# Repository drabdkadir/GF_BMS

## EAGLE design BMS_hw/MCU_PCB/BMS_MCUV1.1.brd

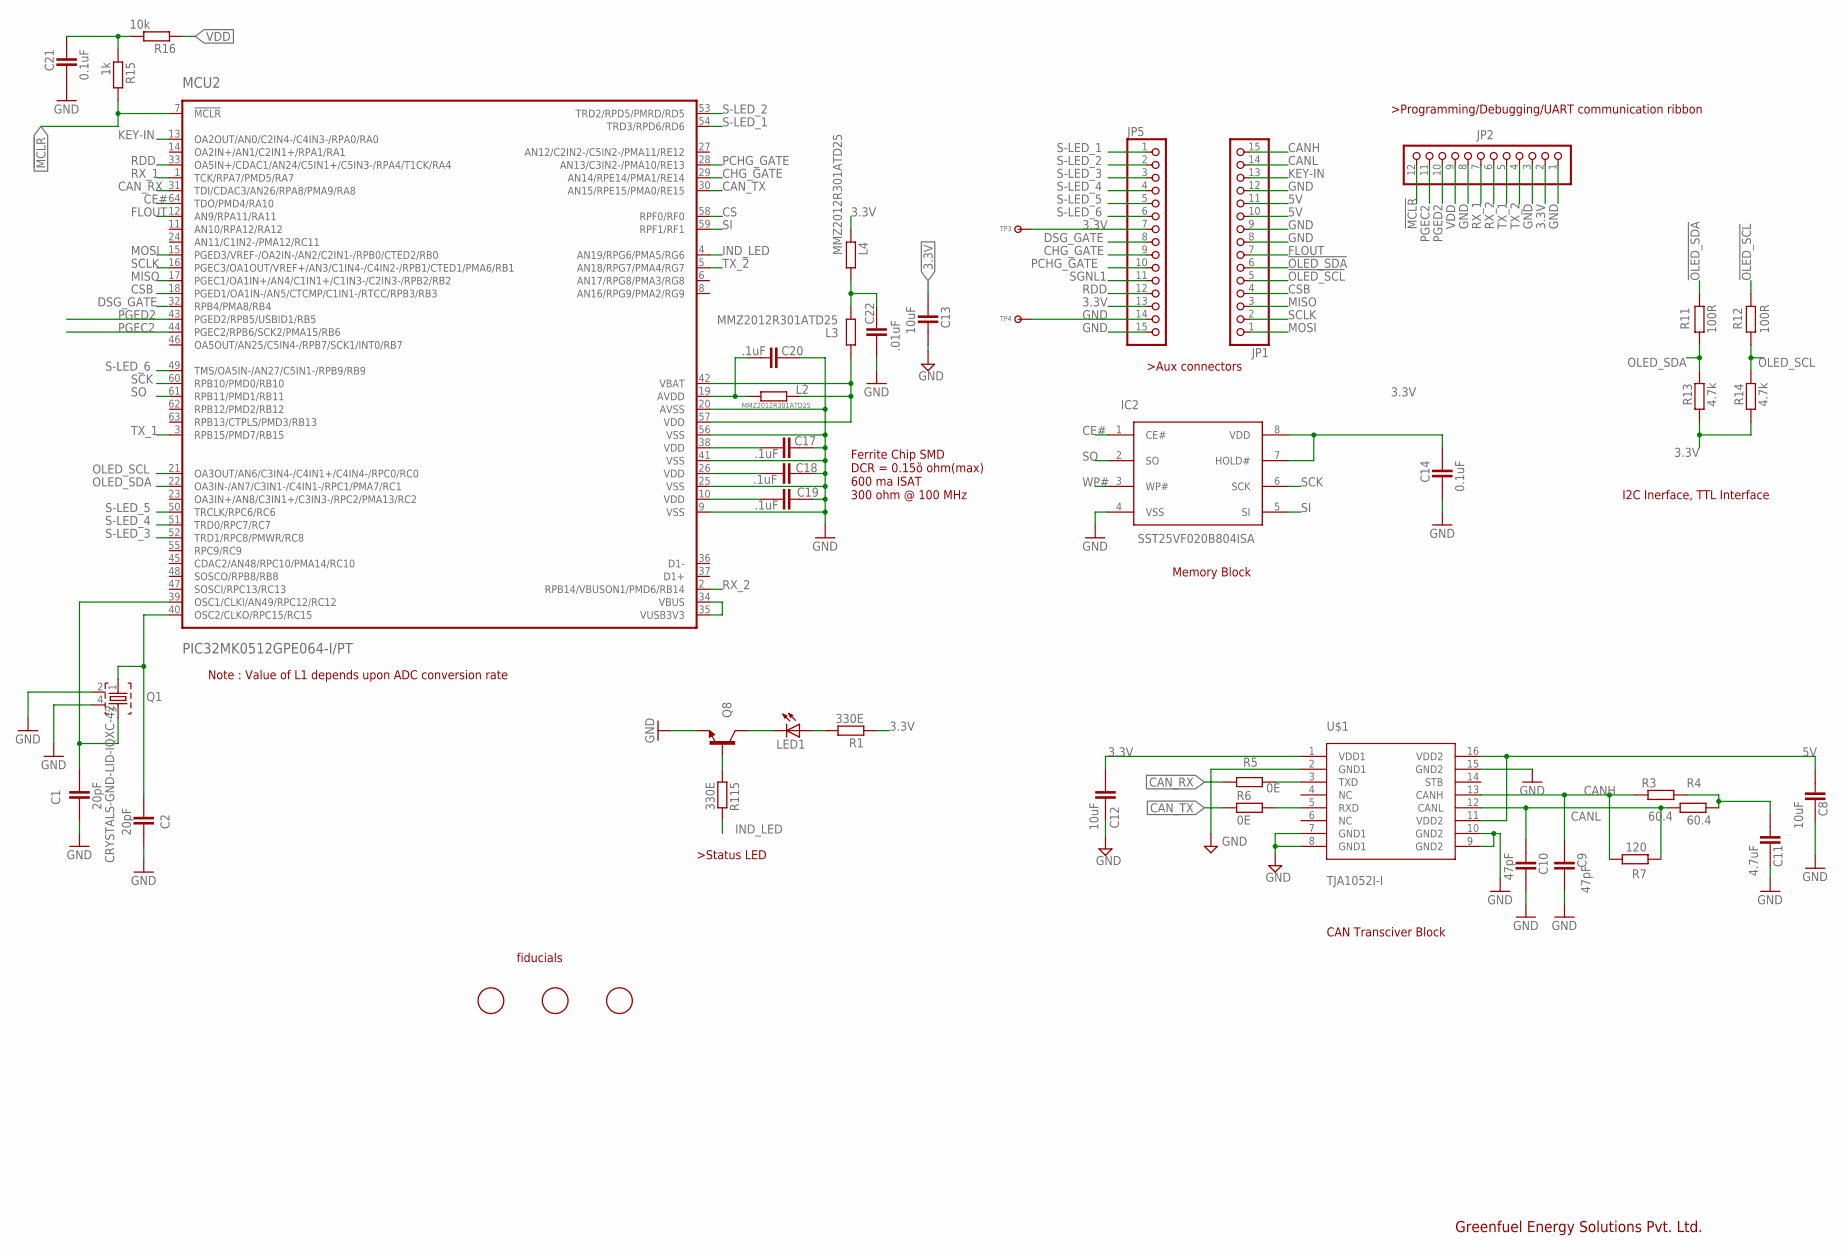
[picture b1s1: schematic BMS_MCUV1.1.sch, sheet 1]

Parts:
C1, C2: 20pF; CAPC1005X60N
C8, C12, C13: 10uF; CAPC1005X60N
C9, C10: 47pF; CAPC1005X60N
C11: 4.7uF; CAPC1005X60N
C14, C21: 0.1uF; CAPC1005X60N
C17, C18, C19, C20: .1uF; CAPC1005X60N
C22: .01uF; CAPC1005X60N
IC2: SST25VF020B804ISA; SOIC127P600X175-8N
JP1, JP5: PINHD-1X15; 1X15
JP2: PINHD-1X12; 1X12X2
L2, L3, L4: MMZ2012R301ATD25; RESC2012X70N
LED1: LEDCHIP-LED0603; CHIP-LED0603
MCU2: PIC32MK0512GPE064-I/PT; TQFP-64-I/PT
Q1: CRYSTALS-GND-LID-IQXC-42; 1.4X1.2-4-PAD
Q8: NPN_SOT-23; SOT95P280X135-3N
R1, R115: 330E; RESC1005X40AN
R3, R4: 60.4; RESC1005X40AN
R5, R6: 0E; RESC1005X40AN
R7: 120; RESC1005X40AN
R11, R12: 100R; RESC1005X40AN
R13, R14: 4.7k; RESC1005X40AN
R15: 1k; RESC1005X40AN
R16: 10k; RESC1005X40AN
TP3, TP4: TP-SMD60
U$1: TJA1052I-I; SOT162-1
U$2, U$3, U$4: FIDUCIAL; FIDUCIAL_1MM

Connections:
3.3V: C12.1, C13.1, C14.1, IC2.7 (HOLD#), IC2.8 (VDD), JP2.2, JP5.7, JP5.13, L4.1, R1.1, R13.1, R14.1, TP3.P$1, U$1.1 (VDD1)
5V: C8.1, JP1.10, JP1.11, U$1.11 (VDD2), U$1.16 (VDD2)
!MCLR: JP2.12, MCU2.7 (!MCLR), R15.2
!OLED_SCL: JP1.5, R12.2
!OLED_SDA: JP1.6, R11.2
AVDD: C20.1, L2.1, MCU2.19 (AVDD)
CANH: C9.1, JP1.15, R3.1, R7.2, U$1.13 (CANH)
CANL: C10.1, JP1.14, R4.1, R7.1, U$1.12 (CANL)
CAN_RX: MCU2.31 (TDI/CDAC3/AN26/RPA8/PMA9/RA8), R5.1
CAN_TX: MCU2.30 (AN15/RPE15/PMA0/RE15), R6.1
CE#: IC2.1 (CE#), MCU2.64 (TDO/PMD4/RA10)
CHG_GATE: JP5.9, MCU2.29 (AN14/RPE14/PMA1/RE14)
CS: MCU2.58 (RPF0/RF0)
CSB: JP1.4, MCU2.18 (PGED1/OA1IN-/AN5/CTCMP/C1IN1-/RTCC/RPB3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)
DSG_GATE: JP5.8, MCU2.32 (RPB4/PMA8/RB4)
FLOUT: JP1.7, MCU2.12 (AN9/RPA11/RA11)
GND: C1.2, C2.2, C8.2, C9.2, C10.2, C11.2, C12.2, C13.2, C14.2, C17.2, C18.2, C19.2, C20.2, C21.2, C22.1, IC2.4 (VSS), JP1.8, JP1.9, JP1.12, JP2.1, JP2.3, JP2.8, JP5.14, JP5.15, MCU2.9 (VSS), MCU2.20 (AVSS), MCU2.25 (VSS), MCU2.41 (VSS), MCU2.56 (VSS), Q1.2, Q1.4, Q8.2 (E), TP4.P$1, U$1.2 (GND1), U$1.7 (GND1), U$1.8 (GND1), U$1.9 (GND2), U$1.10 (GND2), U$1.15 (GND2)
IND_LED: MCU2.4 (AN19/RPG6/PMA5/RG6), R115.2
KEY-IN: JP1.13, MCU2.13 (OA2OUT/AN0/C2IN4-/C4IN3-/RPA0/RA0)
MISO: JP1.3, MCU2.17 (PGEC1/OA1IN+/AN4/C1IN1+/C1IN3-/C2IN3-/R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)
MOSI: JP1.1, MCU2.15 (PGED3/VREF-/OA2IN-/AN2/C2IN1-/RPB0/CTED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)
unnamed: C1.1, MCU2.39 (OSC1/CLKI/AN49/RPC12/RC12), Q1.3
unnamed: C2.1, MCU2.40 (OSC2/CLKO/RPC15/RC15), Q1.1
unnamed: R5.2, U$1.3 (TXD)
unnamed: LED1.A, R1.2
unnamed: R6.2, U$1.5 (RXD)
unnamed: Q8.1 (B), R115.1
unnamed: LED1.C, Q8.3 (C)
unnamed: C22.2, L3.2, L4.2
unnamed: C21.1, R15.1, R16.2
unnamed: MCU2.34 (VBUS), MCU2.35 (VUSB3V3)
OLED_SCL: MCU2.21 (OA3OUT/AN6/C3IN4-/C4IN1+/C4IN4-/RPC0/RC0), R12.1, R14.2
OLED_SDA: MCU2.22 (OA3IN-/AN7/C3IN1-/C4IN1-/RPC1/PMA7/RC1), R11.1, R13.2
PCHG_GATE: JP5.10, MCU2.28 (AN13/C3IN2-/PMA10/RE13)
PGEC2: JP2.11, MCU2.44 (PGEC2/RPB6/SCK2/PMA15/RB6)
PGED2: JP2.10, MCU2.43 (PGED2/RPB5/USBID1/RB5)
R4/R3/C11: C11.1, R3.2, R4.2
RDD: JP5.12, MCU2.33 (OA5IN+/CDAC1/AN24/C5IN1+/C5IN3-/RPA4/T1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)
RX_1: JP2.7, MCU2.1 (TCK/RPA7/PMD5/RA7)
RX_2: JP2.6, MCU2.2 (RPB14/VBUSON1/PMD6/RB14)
S-LED_1: JP5.1, MCU2.54 (TRD3/RPD6/RD6)
S-LED_2: JP5.2, MCU2.53 (TRD2/RPD5/PMRD/RD5)
S-LED_3: JP5.3, MCU2.52 (TRD1/RPC8/PMWR/RC8)
S-LED_4: JP5.4, MCU2.51 (TRD0/RPC7/RC7)
S-LED_5: JP5.5, MCU2.50 (TRCLK/RPC6/RC6)
S-LED_6: JP5.6, MCU2.49 (TMS/OA5IN-/AN27/C5IN1-/RPB9/RB9)
SCK: IC2.6 (SCK), MCU2.60 (RPB10/PMD0/RB10)
SCLK: JP1.2, MCU2.16 (PGEC3/OA1OUT/VREF+/AN3/C1IN4-/C4IN2-/RP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)
SGNL1: JP5.11
SI: IC2.5 (SI), MCU2.59 (RPF1/RF1)
SO: IC2.2 (SO), MCU2.61 (RPB11/PMD1/RB11)
TX_1: JP2.5, MCU2.3 (RPB15/PMD7/RB15)
TX_2: JP2.4, MCU2.5 (AN18/RPG7/PMA4/RG7)
VDD: C17.1, C18.1, C19.1, JP2.9, L2.2, L3.1, MCU2.10 (VDD), MCU2.26 (VDD), MCU2.38 (VDD), MCU2.42 (VBAT), MCU2.57 (VDD), R16.1
WP#: IC2.3 (WP#)

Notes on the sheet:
Note : Value of L1 depends upon ADC conversion rate
CAN Transciver Block
Memory Block
I2C Inerface, TTL Interface
Ferrite Chip SMD DCR = 0.15ȍ ohm(max) 600 ma ISAT 300 ohm @ 100 MHz
Greenfuel Energy Solutions Pvt. Ltd.
fiducials

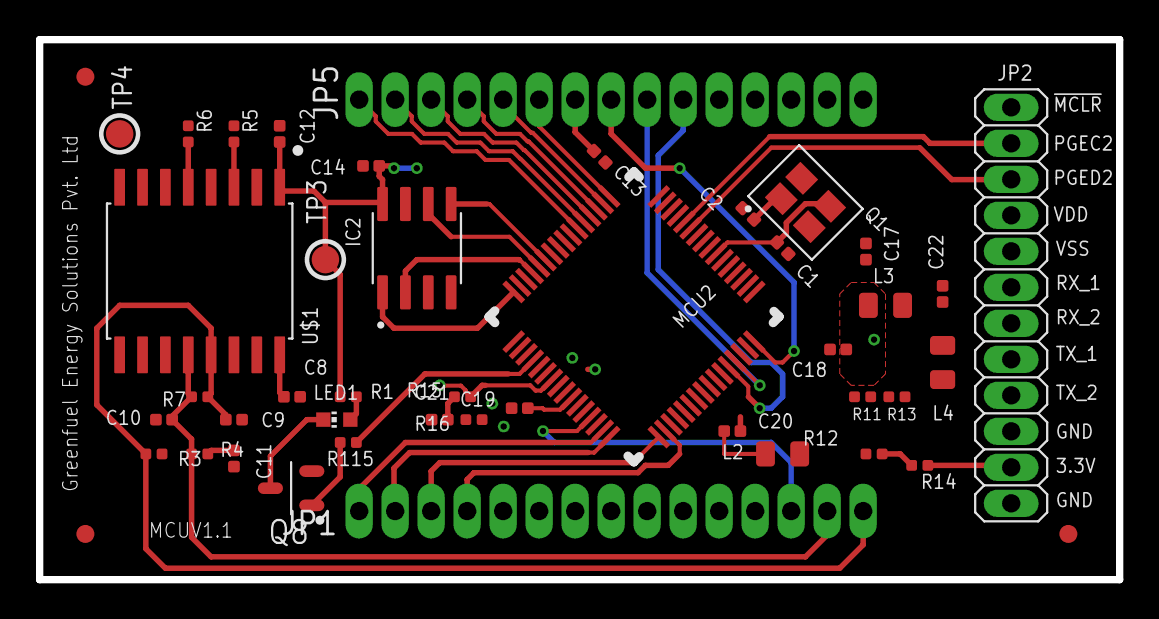
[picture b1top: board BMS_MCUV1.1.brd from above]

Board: 4 copper layers, 60.0 x 30.0 mm, 45 parts (0 on the bottom side), 52 nets.

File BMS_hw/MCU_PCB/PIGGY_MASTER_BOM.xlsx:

GF_AFE board Revised: Sunday, OCT 14, 2018
SCH-XXXXX PDF: SPF-XXXXX Revision: 01
Item | Quantity | ASSY_OPT | Reference | Value | Description | ASSY_NOTE | Mfg Name | Mfg Part Number | PCB Footprint
 | 1 |  | LED1 | Green color | LED GREEN CLEAR CHIP SMD |  | Lite-On Inc. | LTST-C190GKT | SMD 0603
 | 1 |  | Q8 | NPN Transistor | TRANS NPN 40V 0.2A SOT-23 |  | ON Semiconductor | MMBT3904FSCT-ND | SOT-23-3
 | 1 |  | JP2 | 12 pin | 2mm pitch , right angled board to wire 12 pin conn. |  | x | x | Through hole, Right Angle
 | 2 |  | JP1, JP5 | 15 pin | 2mm pitch straight board to board 15 pin conn. |  | x | x | Through hole, straight
 | 1 |  | C22 | 0.01uF/25V | CAP CERAMIC 0.01UF 25V X7R 20% P |  | Murata Electronics North America | GRM155R71E103MA01D | SMD 0402
 | 4 |  | C17, C18, C19, C20,C21,C14 | 0.1uF/16V | CAP CER 0.1UF 16V Y5V 0402 |  | Samsung Electro-Mechanics | CL05F104ZO5NNNC | SMD 0402
 | 2 |  | R5, R6 | 0E | RES SMD 0 OHM JUMP 1/16W 0402 |  | Vishay Dale | CRCW04020000Z0EDC | SMD 0402
 | 2 |  | R11, R12 | 100R | RES SMD 100 OHM 1% 1/16W 0402 |  | Yageo | RC0402FR-07100RL | SMD 0402
 | 1 |  | R16 | 10k | RES TKF 10k 1% 1/10W SMD 0402 |  |  |  | SMD 0402
 | 3 |  | C8, C12, C13 | 10uF/10V | CAP CER 10UF 10V X5R 0402 |  | AVX Corporation | 0402ZD106MAT2A | SMD 0402
 | 1 |  | R7 | 120E | RES 120 OHM 1% 1/16W 0402 |  | Samsung Electro-Mechanics | RCS1005F121CS | SMD 0402
 | 1 |  | R15 | 1k | RES SMD 1K OHM 0.5% 1/16W 0402 |  | Susumu | RR0510P-102-D | SMD 0402
 | 2 |  | C1, C2 | 20pF | CAP CER 20PF 50V C0G/NP0 0402 |  | Murata Electronics North America | GJM1555C1H200JB01D | SMD 0402
 | 2 |  | R1, R115 | 330E | RES SMD 330 OHM 1% 1/10W 0402 |  | Panasonic Electronic Components | ERJ-2RKF3300X | SMD 0402
 | 2 |  | R13, R14 | 4.7k | RES SMD 4.7K OHM 1% 1/16W 0402 |  | Yageo | RC0402FR-074K7L | SMD 0402
 | 1 |  | C11 | 4.7uF | CAP CER 4.7UF 16V X5R 0402 |  | Samsung Electro-Mechanics | CL05A475MO5NUNC | SMD 0402
 | 2 |  | C9, C10 | 47pF | CAP CER 47PF 50V C0G/NP0 0402 |  | AVX Corporation | 04025A470JAT2A | SMD 0402
 | 2 |  | R3, R4 | 60.4E | RES SMD 60.4 OHM 1% 1/10W 0402 |  | Panasonic Electronic Components | ERJ-2RKF60R4X | SMD 0402
 | 1 |  | Q1 | CRYSTALS-GND-LID-IQXC-42 | CRYSTAL 12.0000MHZ 12PF SMD |  | EPSON | FA-238V 12.0000MB-W3 | 4-SMD, No Lead
 | 3 |  | L2, L3, L4 | MMZ2012R301ATD25 | FERRITE BEAD 300 OHM 0805 1LN |  | TDK Corporation | MMZ2012R301ATD25 | SMD 0805
 | 1 |  | MCU2 | PIC32MK0512GPE064-I/PT | IC MCU 32BIT 512KB FLASH 64TQFP |  | Microchip Technology | PIC32MK0512GPE064-I/PT | 64-TQFP
 | 1 |  | IC2 | SST25VF020B804ISA | IC FLASH 2M SPI 80MHZ 8SOIC |  | Microchip Technology | SST25VF020B-80-4I-SAE | 8-SOIC (0.154", 3.90mm Width)
 | 1 |  | U$1 | TJA1052I-I | DGTL ISOLATOR 5KV 2CH CAN 16SO |  | NXP USA Inc. | TJA1052IT/5Y | 16-SOIC (0.295", 7.50mm Width)

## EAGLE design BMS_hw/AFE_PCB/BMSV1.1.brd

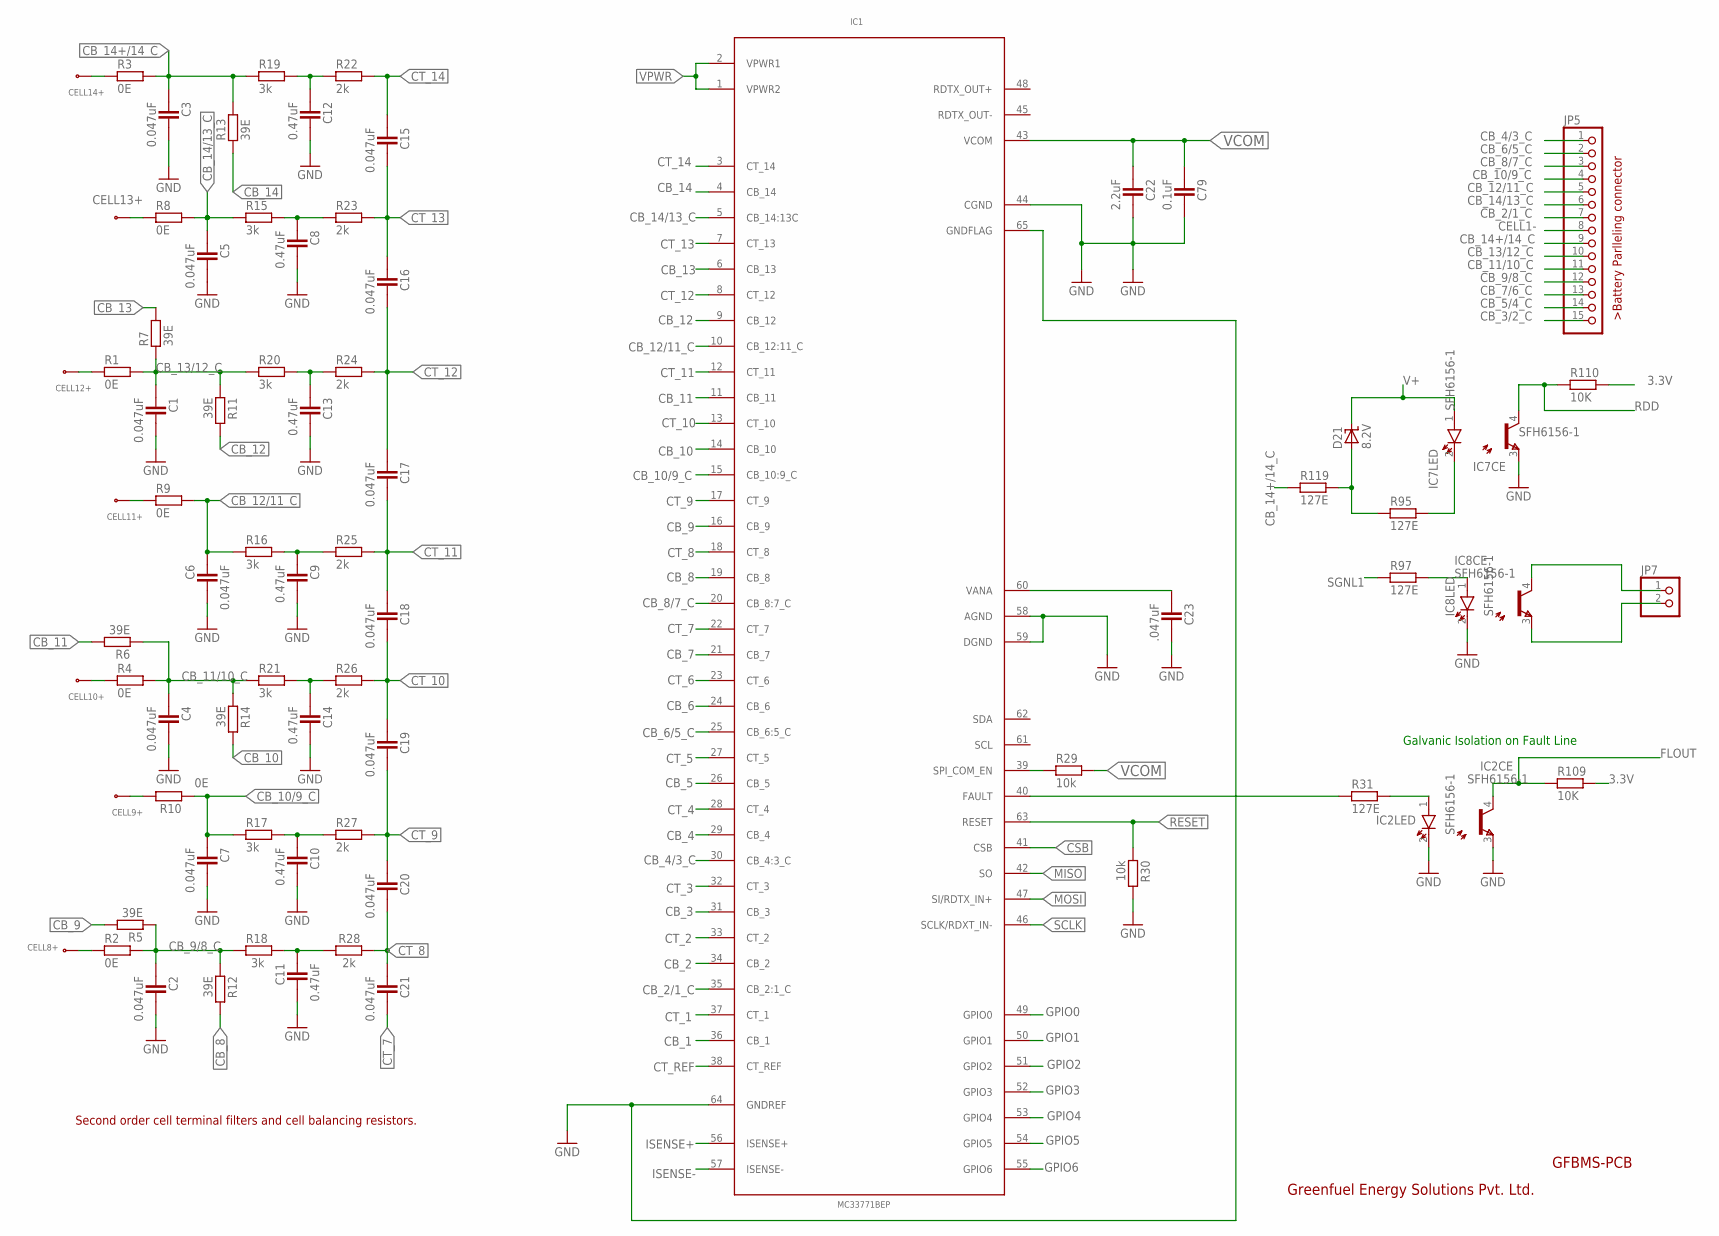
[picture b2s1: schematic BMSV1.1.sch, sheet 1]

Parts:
C1, C2, C3, C4, C5, C6, C7: 0.047uF; CAPC1608X92N
C8, C9, C10, C11, C12, C13, C14: 0.47uF; CAPC3215X168N
C15, C16, C17, C18, C19, C20, C21: 0.047uF; CAPC1005X60N
C22: 2.2uF; CAPC1608X92N
C23: .047uF; CAPC1005X60N
C79: 0.1uF; CAPC1608X92N
CELL8+, CELL9+, CELL10+, CELL11+, CELL12+, CELL13+, CELL14+: GF_BMS_CELL_PADP_PAD; CELL_PAD
D21: 8.2V; SOD3718X135N
IC1: MC33771BEP; 64PIN-LQFP
IC2, IC7, IC8: SFH6156-1; SFH
JP5: PINHD-1X15; 1X15
JP7: PINHD-1X2; 1X02
R1, R2, R3, R4, R8, R9, R10: 0E; RESC1005X40AN
R5, R6, R7, R11, R12, R13, R14: 39E; RESC3225X70N
R15, R16, R17, R18, R19, R20, R21: 3k; RESC1005X40AN
R22, R23, R24, R25, R26, R27, R28: 2k; RESC1005X40AN
R29, R30: 10k; RESC1005X40AN
R31, R95, R97, R119: 127E; RESC1608X55N
R109, R110: 10K; RESC1005X40AN

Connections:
3.3V: R109.2, R110.2; also elsewhere on the board
CB_1: IC1.36 (CB_1); also elsewhere on the board
CB_2: IC1.34 (CB_2); also elsewhere on the board
CB_2/1_C: IC1.35 (CB_2:1_C), JP5.7; also elsewhere on the board
CB_3: IC1.31 (CB_3); also elsewhere on the board
CB_3/2_C: JP5.15; also elsewhere on the board
CB_4: IC1.29 (CB_4); also elsewhere on the board
CB_4/3_C: IC1.30 (CB_4:3_C), JP5.1; also elsewhere on the board
CB_5: IC1.26 (CB_5); also elsewhere on the board
CB_5/4_C: JP5.14; also elsewhere on the board
CB_6: IC1.24 (CB_6); also elsewhere on the board
CB_6/5_C: IC1.25 (CB_6:5_C), JP5.2; also elsewhere on the board
CB_7: IC1.21 (CB_7); also elsewhere on the board
CB_7/6_C: JP5.13; also elsewhere on the board
CB_8: IC1.19 (CB_8), R12.2
CB_8/7_C: IC1.20 (CB_8:7_C), JP5.3; also elsewhere on the board
CB_9: IC1.16 (CB_9), R5.2
CB_9/8_C: C2.1, JP5.12, R2.2, R5.1, R12.1, R18.1
CB_10: IC1.14 (CB_10), R14.2
CB_10/9_C: C7.1, IC1.15 (CB_10:9_C), JP5.4, R10.1, R17.1; also elsewhere on the board
CB_11: IC1.11 (CB_11), R6.2
CB_11/10_C: C4.1, JP5.11, R4.2, R6.1, R14.1, R21.1
CB_12: IC1.9 (CB_12), R11.2; also elsewhere on the board
CB_12/11_C: C6.1, IC1.10 (CB_12:11_C), JP5.5, R9.2, R16.1
CB_13: IC1.6 (CB_13), R7.2
CB_13/12_C: C1.1, JP5.10, R1.2, R7.1, R11.1, R20.1
CB_14: IC1.4 (CB_14), R13.1; also elsewhere on the board
CB_14+/14_C: C3.1, JP5.9, R3.2, R13.2, R19.1, R119.1; also elsewhere on the board
CB_14/13_C: C5.1, IC1.5 (CB_14:13C), JP5.6, R8.2, R15.1
CELL1-: JP5.8; also elsewhere on the board
CELL8+: CELL8+.P$1, R2.1
CELL9+: CELL9+.P$1, R10.2
CELL10+: CELL10+.P$1, R4.1
CELL11+: CELL11+.P$1, R9.1
CELL12+: CELL12+.P$1, R1.1
CELL13+: CELL13+.P$1, R8.1
CELL14+: CELL14+.P$1, R3.1; also elsewhere on the board
CSB: IC1.41 (CSB); also elsewhere on the board
CT_1: IC1.37 (CT_1); also elsewhere on the board
CT_2: IC1.33 (CT_2); also elsewhere on the board
CT_3: IC1.32 (CT_3); also elsewhere on the board
CT_4: IC1.28 (CT_4); also elsewhere on the board
CT_5: IC1.27 (CT_5); also elsewhere on the board
CT_6: IC1.23 (CT_6); also elsewhere on the board
CT_7: C21.2, IC1.22 (CT_7); also elsewhere on the board
CT_8: C20.2, C21.1, IC1.18 (CT_8), R28.2
CT_9: C19.2, C20.1, IC1.17 (CT_9), R27.2
CT_10: C18.2, C19.1, IC1.13 (CT_10), R26.2
CT_11: C17.2, C18.1, IC1.12 (CT_11), R25.2
CT_12: C16.2, C17.1, IC1.8 (CT_12), R24.2
CT_13: C15.2, C16.1, IC1.7 (CT_13), R23.2
CT_14: C15.1, IC1.3 (CT_14), R22.2
CT_REF: IC1.38 (CT_REF); also elsewhere on the board
FLOUT: IC2.4 (C), R109.1; also elsewhere on the board
GND: C1.2, C2.2, C3.2, C4.2, C5.2, C6.2, C7.2, C8.2, C9.2, C10.2, C11.2, C12.2, C13.2, C14.2, C22.2, C23.2, C79.2, IC1.44 (CGND), IC1.58 (AGND), IC1.59 (DGND), IC1.64 (GNDREF), IC1.65 (GNDFLAG), IC2.2 (K), IC2.3 (E), IC7.3 (E), IC8.2 (K), R30.2; also elsewhere on the board
GPIO0: IC1.49 (GPIO0); also elsewhere on the board
GPIO1: IC1.50 (GPIO1); also elsewhere on the board
GPIO2: IC1.51 (GPIO2); also elsewhere on the board
GPIO3: IC1.52 (GPIO3); also elsewhere on the board
GPIO4: IC1.53 (GPIO4); also elsewhere on the board
GPIO5: IC1.54 (GPIO5); also elsewhere on the board
GPIO6: IC1.55 (GPIO6); also elsewhere on the board
ISENSE+: IC1.56 (ISENSE+); also elsewhere on the board
ISENSE-: IC1.57 (ISENSE-); also elsewhere on the board
MISO: IC1.42 (SO); also elsewhere on the board
MOSI: IC1.47 (SI/RDTX_IN+); also elsewhere on the board
unnamed: C12.1, R19.2, R22.1
unnamed: C11.1, R18.2, R28.1
unnamed: C14.1, R21.2, R26.1
unnamed: C13.1, R20.2, R24.1
unnamed: C8.1, R15.2, R23.1
unnamed: C10.1, R17.2, R27.1
unnamed: C9.1, R16.2, R25.1
unnamed: IC8.4 (C), JP7.1
unnamed: IC8.3 (E), JP7.2
unnamed: IC7.2 (K), R95.2
unnamed: IC8.1 (A), R97.2
unnamed: IC1.40 (FAULT), R31.1
unnamed: IC2.1 (A), R31.2
unnamed: IC1.39 (SPI_COM_EN), R29.1
unnamed: D21.A, R95.1, R119.2
RDD: IC7.4 (C), R110.1; also elsewhere on the board
RESET: IC1.63 (RESET), R30.1
SCLK: IC1.46 (SCLK/RDXT_IN-); also elsewhere on the board
SGNL1: R97.1; also elsewhere on the board
V+: D21.K, IC7.1 (A); also elsewhere on the board
VANA: C23.1, IC1.60 (VANA)
VCOM: C22.1, C79.1, IC1.43 (VCOM), R29.2; also elsewhere on the board
VPWR: IC1.1 (VPWR2), IC1.2 (VPWR1); also elsewhere on the board

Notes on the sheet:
Galvanic Isolation on Fault Line
Second order cell terminal filters and cell balancing resistors.
Greenfuel Energy Solutions Pvt. Ltd.
GFBMS-PCB

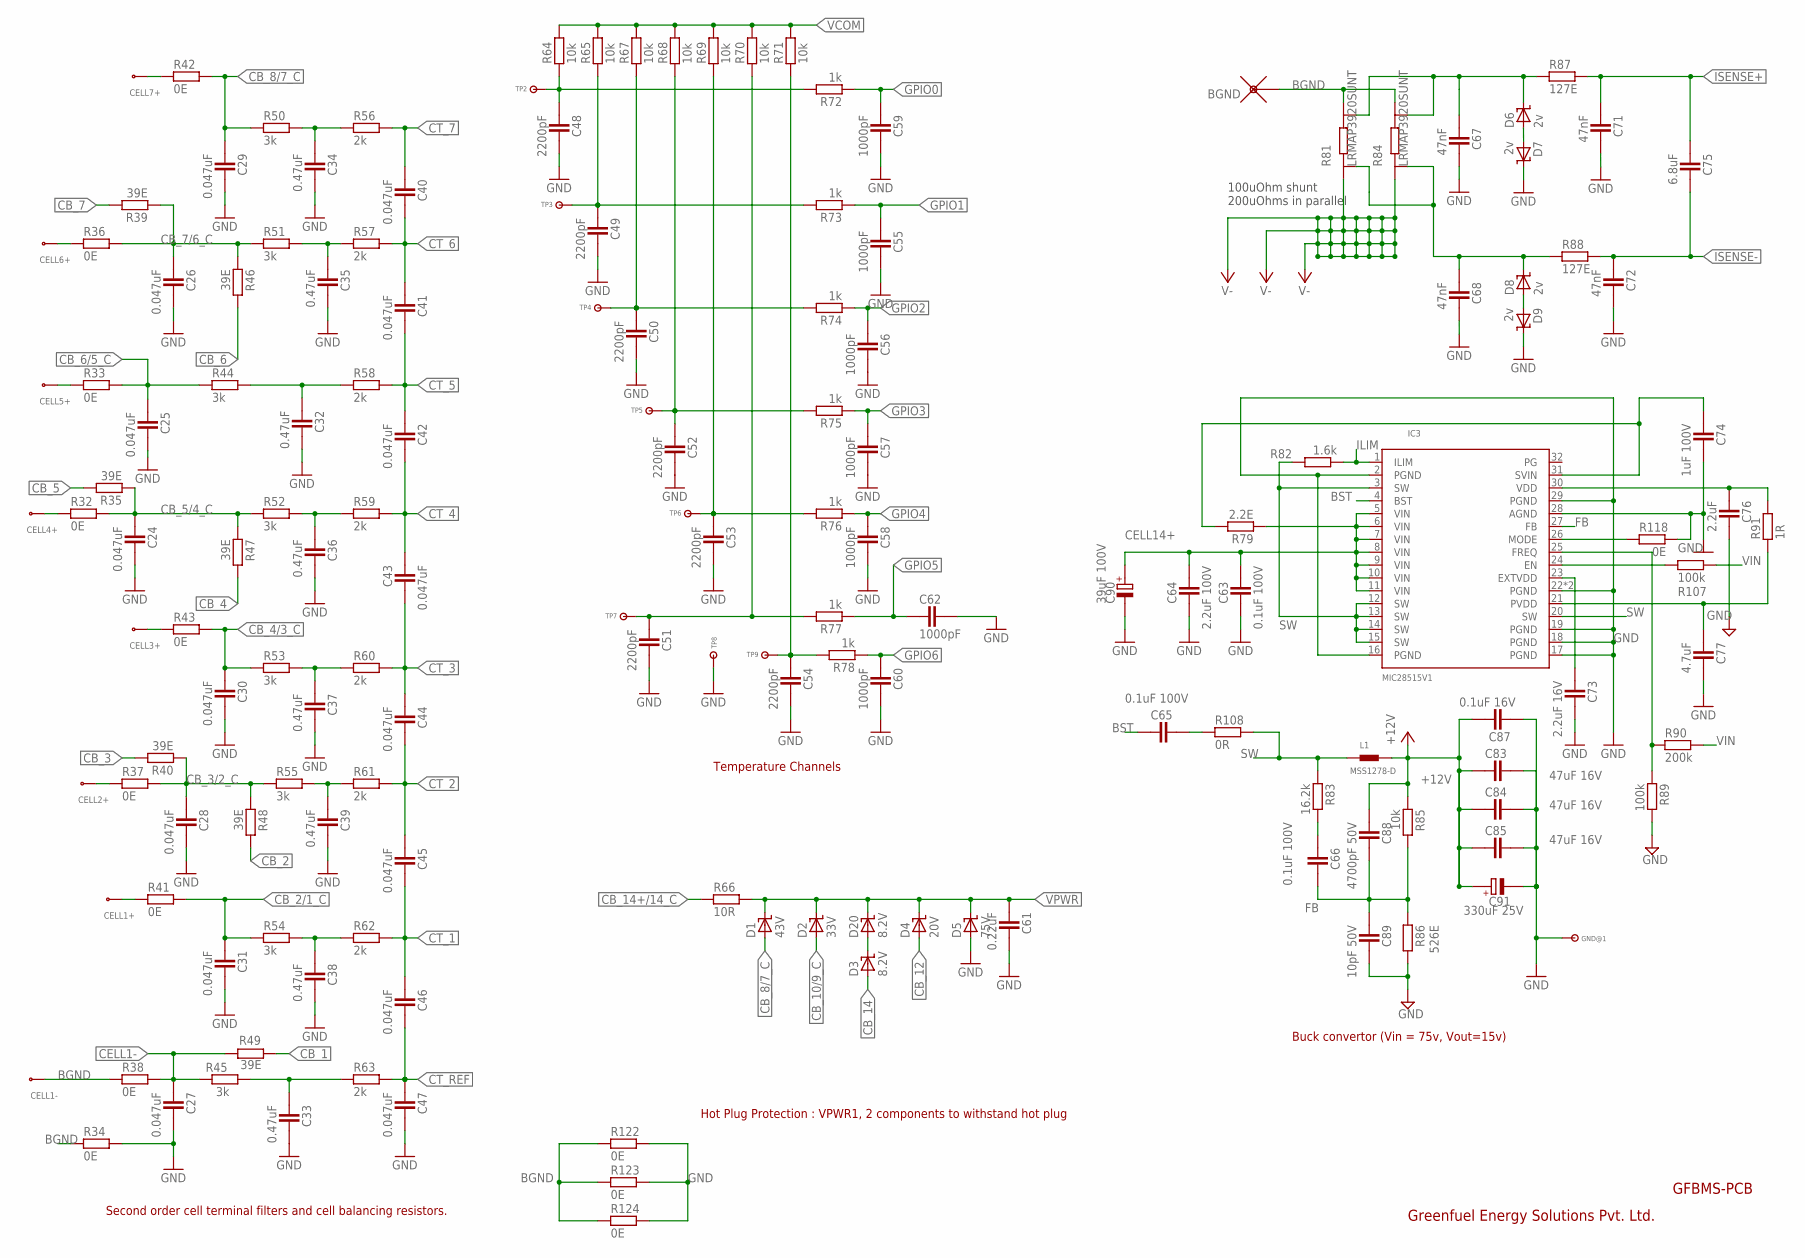
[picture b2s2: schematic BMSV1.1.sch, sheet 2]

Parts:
BGND: WPAD
C24, C25, C26, C27, C28, C29, C30, C31: 0.047uF; CAPC1608X92N
C32, C33, C34, C35, C36, C37, C38, C39: 0.47uF; CAPC3215X168N
C40, C41, C42, C43, C44, C45, C46, C47: 0.047uF; CAPC1005X60N
C48, C49, C50, C51, C52, C53, C54: 2200pF; CAPC1005X60N
C55, C56, C57, C58, C59, C60, C62: 1000pF; CAPC1005X60N
C61: 0.22uF; CAPC2012X145AN
C63, C65, C66: 0.1uF 100V; CAPC1608X92N
C64: 2.2uF 100V; CAPC3225X168N
C67, C68: 47nF; CAPC1608X92N
C71, C72: 47nF; CAPC1005X60N
C73: 2.2uF 16V; CAPC1608X92N
C74: 1uF 100V; CAPC2012X145AN
C75: 6.8uF; CAPC2012X145AN
C76: 2.2uF; CAPC1608X92N
C77: 4.7uF; CAPC2012X145AN
C83, C84, C85: 47uF 16V; CAPC3225X168N
C87: 0.1uF 16V; CAPC1608X92N
C88: 4700pF 50V; CAPC1608X92N
C89: 10pF 50V; CAPC1608X92N
C90: 39uF 100V; CAPAE830X1020N
C91: 330uF 25V; CAPAE830X1020N
CELL1+, CELL1-, CELL2+, CELL3+, CELL4+, CELL5+, CELL6+, CELL7+: GF_BMS_CELL_PADP_PAD; CELL_PAD
D1: 43V; SOD2514X100N
D2: 33V; SOD3718X135N
D3, D20: 8.2V; SOD3718X135N
D4: 20V; SOD3718X135N
D5: 75V; SOD3718X135N
D6, D7, D8, D9: 2v; SOD3718X135N
GND@1: TP-SMD60
IC3: MIC28515V1; VQFN-32
L1: MSS1278-D; MSS1278D/T
R32, R33, R34, R36, R37, R38, R41, R42, R43, R118, R122, R123, R124: 0E; RESC1005X40AN
R35, R39, R40, R46, R47, R48, R49: 39E; RESC3225X70N
R44, R45, R50, R51, R52, R53, R54, R55: 3k; RESC1005X40AN
R56, R57, R58, R59, R60, R61, R62, R63: 2k; RESC1005X40AN
R64, R65, R67, R68, R69, R70, R71: 10k; RESC1005X40AN
R66: 10R; RESC1608X55N
R72, R73, R74, R75, R76, R77, R78: 1k; RESC1005X40AN
R79: 2.2E; RESC1608X55N
R81, R84: LRMAP3920SUNT; SMD4
R82: 1.6k; RESC1608X55N
R83: 16.2k; RESC1608X55N
R85: 10k; RESC1608X55N
R86: 526E; RESC1608X55N
R87, R88: 127E; RESC1608X55N
R89, R107: 100k; RESC1608X55N
R90: 200k; RESC1608X55N
R91: 1R; RESC1608X55N
R108: 0R; RESC1005X40AN
TP2, TP3, TP4, TP5, TP6, TP7, TP8, TP9: TPTH7035; TP7035

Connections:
+12V: C83.1, C84.1, C85.1, C87.2, C88.1, C91.+, L1.2, R85.1; also elsewhere on the board
BGND: BGND.1, CELL1-.P$1, R34.1, R38.1, R81.4, R81.6 (4), R84.4, R84.6 (4), R122.1, R123.1, R124.1; also elsewhere on the board
BST: C65.1, IC3.4 (BST)
CB_1: R49.2; also elsewhere on the board
CB_2: R48.2; also elsewhere on the board
CB_2/1_C: C31.1, R41.2, R54.1; also elsewhere on the board
CB_3: R40.2; also elsewhere on the board
CB_3/2_C: C28.1, R37.2, R40.1, R48.1, R55.1; also elsewhere on the board
CB_4: R47.2; also elsewhere on the board
CB_4/3_C: C30.1, R43.2, R53.1; also elsewhere on the board
CB_5: R35.2; also elsewhere on the board
CB_5/4_C: C24.1, R32.2, R35.1, R47.1, R52.1; also elsewhere on the board
CB_6: R46.2; also elsewhere on the board
CB_6/5_C: C25.1, R33.2, R44.1; also elsewhere on the board
CB_7: R39.2; also elsewhere on the board
CB_7/6_C: C26.1, R36.2, R39.1, R46.1, R51.1; also elsewhere on the board
CB_8/7_C: C29.1, D1.A, R42.2, R50.1; also elsewhere on the board
CB_10/9_C: D2.A; also elsewhere on the board
CB_12: D4.A; also elsewhere on the board
CB_14: D3.A; also elsewhere on the board
CB_14+/14_C: R66.1; also elsewhere on the board
CELL1+: CELL1+.P$1, R41.1
CELL1-: C27.1, R38.2, R45.1, R49.1; also elsewhere on the board
CELL2+: CELL2+.P$1, R37.1
CELL3+: CELL3+.P$1, R43.1
CELL4+: CELL4+.P$1, R32.1
CELL5+: CELL5+.P$1, R33.1
CELL6+: CELL6+.P$1, R36.1
CELL7+: CELL7+.P$1, R42.1
CELL14+: C63.2, C64.2, C90.+, IC3.5 (VIN), IC3.6 (VIN), IC3.7 (VIN), IC3.8 (VIN), IC3.9 (VIN), IC3.10 (VIN), IC3.11 (VIN), R79.1; also elsewhere on the board
CT_1: C45.2, C46.1, R62.2; also elsewhere on the board
CT_2: C44.2, C45.1, R61.2; also elsewhere on the board
CT_3: C43.2, C44.1, R60.2; also elsewhere on the board
CT_4: C42.2, C43.1, R59.2; also elsewhere on the board
CT_5: C41.2, C42.1, R58.2; also elsewhere on the board
CT_6: C40.2, C41.1, R57.2; also elsewhere on the board
CT_7: C40.1, R56.2; also elsewhere on the board
CT_REF: C46.2, C47.1, R63.2; also elsewhere on the board
FB: C66.2, C88.2, C89.1, IC3.27 (FB), R85.2, R86.1
GND: C24.2, C25.2, C26.2, C27.2, C28.2, C29.2, C30.2, C31.2, C32.2, C33.2, C34.2, C35.2, C36.2, C37.2, C38.2, C39.2, C47.2, C48.2, C49.2, C50.2, C51.2, C52.2, C53.2, C54.2, C55.2, C56.2, C57.2, C58.2, C59.2, C60.2, C61.2, C62.2, C63.1, C64.1, C67.2, C68.2, C71.2, C72.2, C73.2, C74.2, C76.2, C77.2, C83.2, C84.2, C85.2, C87.1, C89.2, C90.-, C91.-, D5.A, D7.K, D9.K, GND@1.P$1, IC3.2 (PGND), IC3.16 (PGND), IC3.17 (PGND), IC3.18 (PGND), IC3.19 (PGND), IC3.22 (PGND), IC3.28 (AGND), IC3.29 (PGND), IC3.33 (PGND), R34.2, R86.2, R89.2, R118.2, R122.2, R123.2, R124.2, TP8.P$1; also elsewhere on the board
GPIO0: C59.1, R72.1; also elsewhere on the board
GPIO1: C55.1, R73.1; also elsewhere on the board
GPIO2: C56.1, R74.1; also elsewhere on the board
GPIO3: C57.1, R75.1; also elsewhere on the board
GPIO4: C58.1, R76.1; also elsewhere on the board
GPIO5: C62.1, R77.1; also elsewhere on the board
GPIO6: C60.1, R78.1; also elsewhere on the board
ILIM: IC3.1 (ILIM), R82.1
ISENSE+: C71.1, C75.1, R87.2; also elsewhere on the board
ISENSE-: C72.1, C75.2, R88.2; also elsewhere on the board
unnamed: D8.A, D9.A
unnamed: C32.1, R44.2, R58.1
unnamed: C38.1, R54.2, R62.1
unnamed: D6.A, D7.A
unnamed: IC3.24 (EN), R107.1
unnamed: C65.2, R108.1
unnamed: C37.1, R53.2, R60.1
unnamed: IC3.25 (FREQ), R89.1, R90.1
unnamed: C73.1, IC3.23 (EXTVDD)
unnamed: C74.1, IC3.31 (SVIN), R79.2
unnamed: C36.1, R52.2, R59.1
unnamed: C66.1, R83.2
unnamed: D3.K, D20.A
unnamed: C35.1, R51.2, R57.1
unnamed: C34.1, R50.2, R56.1
unnamed: C39.1, R55.2, R61.1
unnamed: C33.1, R45.2, R63.1
unnamed: C48.1, R64.1, R72.2, TP2.P$1
unnamed: C49.1, R65.1, R73.2, TP3.P$1
unnamed: C50.1, R67.1, R74.2, TP4.P$1
unnamed: C52.1, R68.1, R75.2, TP5.P$1
unnamed: C53.1, R69.1, R76.2, TP6.P$1
unnamed: C51.1, R70.1, R77.2, TP7.P$1
unnamed: C54.1, R71.1, R78.2, TP9.P$1
unnamed: IC3.26 (MODE), R118.1
unnamed: C67.1, D6.K, R81.5, R84.5, R87.1
unnamed: C68.1, D8.K, R81.2, R84.2, R88.1
PVDD: C77.1, IC3.21 (PVDD), R91.1
SW: IC3.3 (SW), IC3.12 (SW), IC3.13 (SW), IC3.14 (SW), IC3.15 (SW), IC3.20 (SW), L1.1, R82.2, R83.1, R108.2
V-: R81.1, R81.3 (1), R84.1, R84.3 (1); also elsewhere on the board
VCOM: R64.2, R65.2, R67.2, R68.2, R69.2, R70.2, R71.2; also elsewhere on the board
VDD: C76.1, IC3.30 (VDD), R91.2
VIN: R90.2, R107.2
VPWR: C61.1, D1.K, D2.K, D4.K, D5.K, D20.K, R66.2; also elsewhere on the board

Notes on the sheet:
Second order cell terminal filters and cell balancing resistors.
Temperature Channels
Hot Plug Protection : VPWR1, 2 components to withstand hot plug
100uOhm shunt 200uOhms in parallel
Greenfuel Energy Solutions Pvt. Ltd.
GFBMS-PCB
Buck convertor (Vin = 75v, Vout=15v)
